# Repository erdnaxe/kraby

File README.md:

# Kraby

Kraby is an hexapod robot.
It is an open source development platform for educational purpose.
It was designed for a Master 1
project at [ENS Paris-Saclay](https://ens-paris-saclay.fr/).

You may read documentation at <https://kraby.readthedocs.io/>

## Build the documentation

Install `mkdocs` then run `mkdocs serve`.

## Install OpenAI environment

```bash
pip install gym_kraby --user
python -m gym_kraby.demo
```

To test servomotors communication with the robot, you may execute `python -m gym_kraby.utils.herkulex_socket`.

## License

This project is under MIT License because we believe in
open development. Please see LICENSE file for more details.

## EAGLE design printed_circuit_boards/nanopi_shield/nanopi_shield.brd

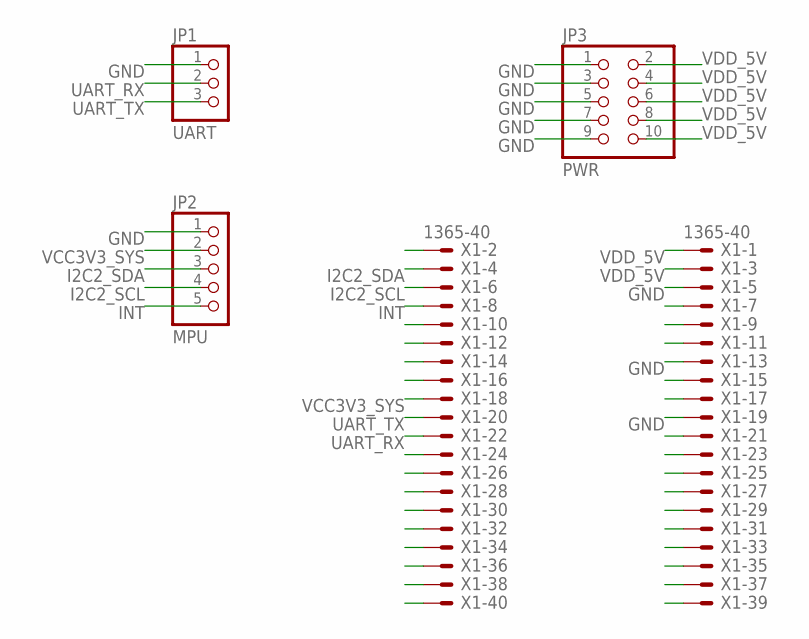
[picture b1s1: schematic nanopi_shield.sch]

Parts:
JP1: UART; 1X03
JP2: MPU; 1X05
JP3: PWR; 2X05
X1: 1365-40

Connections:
GND: JP1.1, JP2.1, JP3.1, JP3.3, JP3.5, JP3.7, JP3.9, X1.5, X1.13, X1.19
I2C2_SCL: JP2.4, X1.6
I2C2_SDA: JP2.3, X1.4
INT: JP2.5, X1.8
UART_RX: JP1.2, X1.22
UART_TX: JP1.3, X1.20
VCC3V3_SYS: JP2.2, X1.18
VDD_5V: JP3.2, JP3.4, JP3.6, JP3.8, JP3.10, X1.1, X1.3

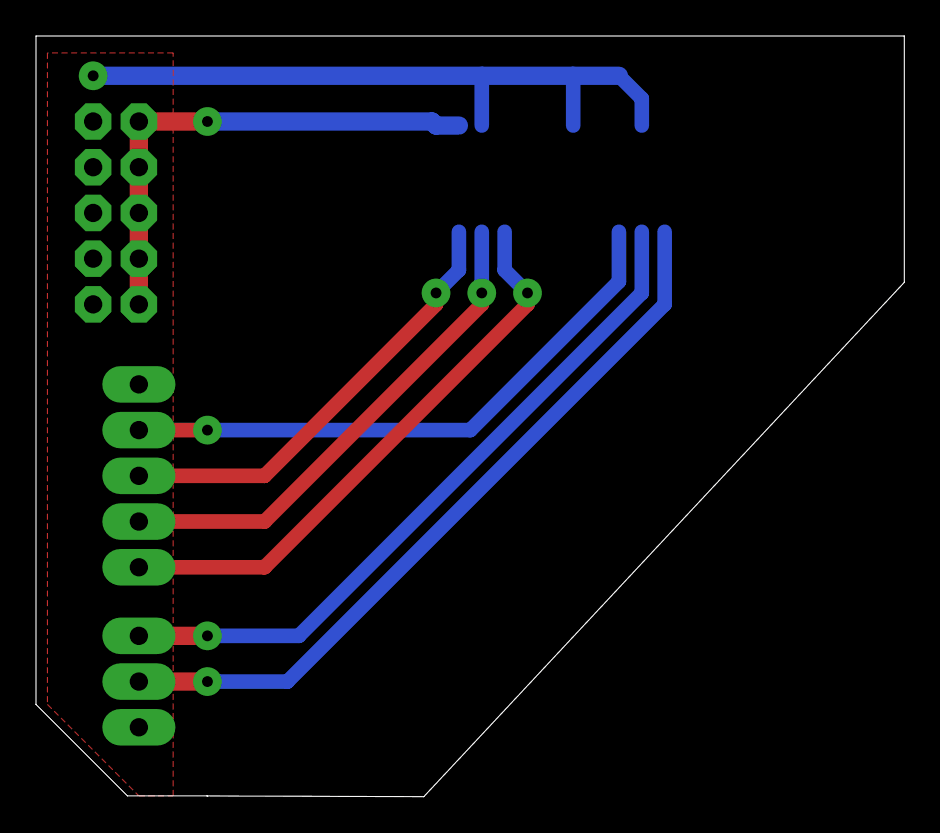
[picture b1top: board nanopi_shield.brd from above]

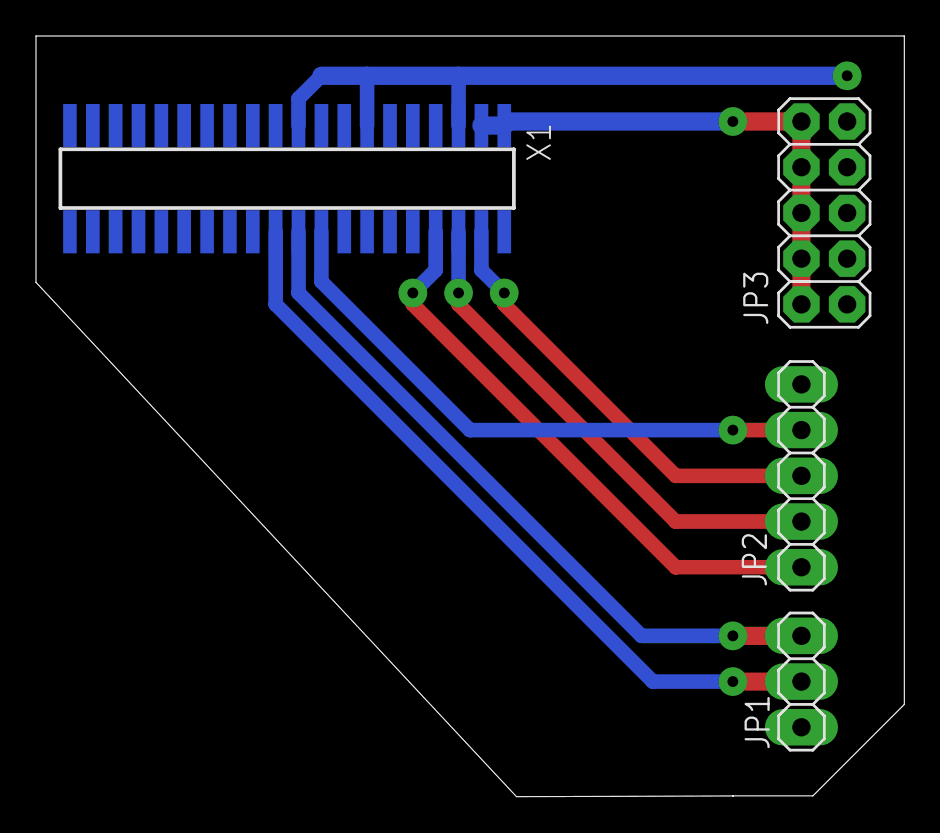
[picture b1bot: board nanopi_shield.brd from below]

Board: 2 copper layers, 48.2 x 42.3 mm, 4 parts (4 on the bottom side), 8 nets.

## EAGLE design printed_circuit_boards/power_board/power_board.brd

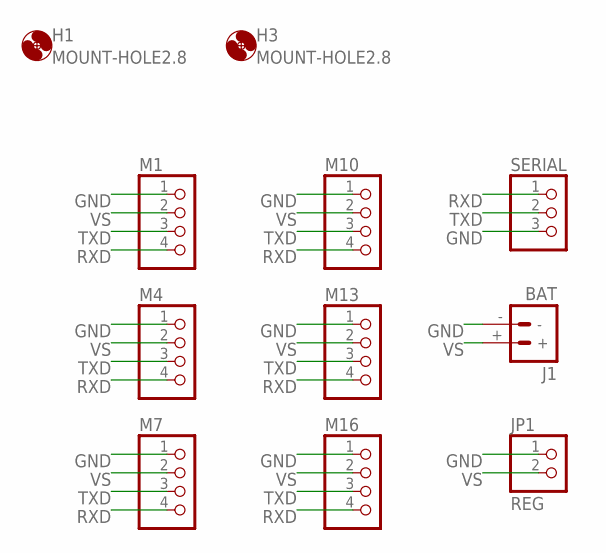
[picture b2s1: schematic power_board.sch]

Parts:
H1, H3: MOUNT-HOLE2.8; 2,8
J1: BAT; DEANS
JP1: REG; 1X02
M1, M4, M7, M10, M13, M16: PINHD-1X4; 1X04
SERIAL: PINHD-1X3; 1X03

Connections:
GND: J1.-, JP1.1, M1.1, M4.1, M7.1, M10.1, M13.1, M16.1, SERIAL.3
RXD: M1.4, M4.4, M7.4, M10.4, M13.4, M16.4, SERIAL.1
TXD: M1.3, M4.3, M7.3, M10.3, M13.3, M16.3, SERIAL.2
VS: J1.+, JP1.2, M1.2, M4.2, M7.2, M10.2, M13.2, M16.2

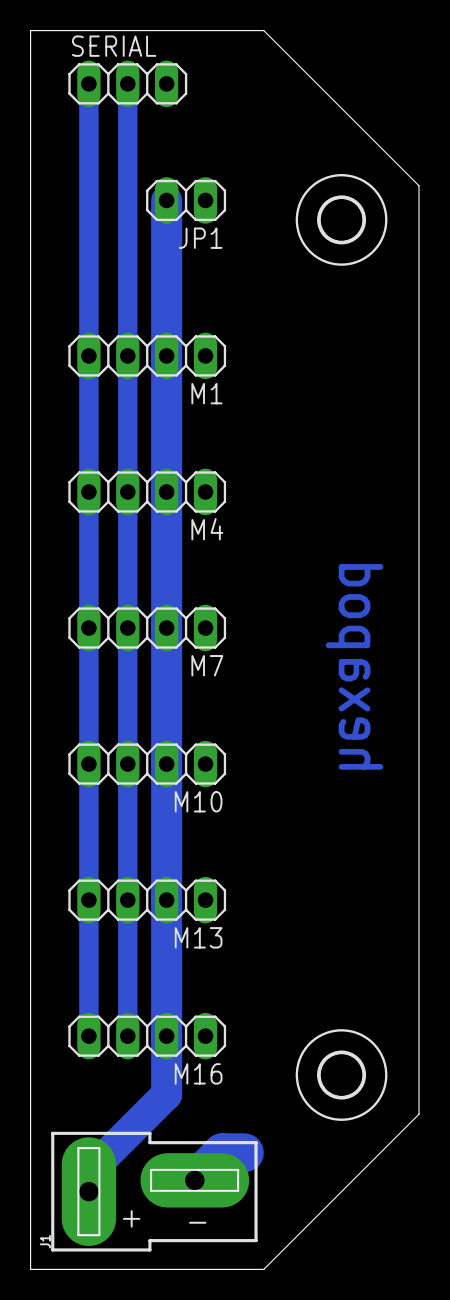
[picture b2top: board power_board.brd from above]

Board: 2 copper layers, 25.3 x 80.8 mm, 11 parts (0 on the bottom side), 4 nets.

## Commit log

2020-02-14 Power board
2020-02-18 Add NanoPi Neo4 shield
2020-02-18 Round corner
2020-02-19 Larger pads
2020-02-19 Add pdf for NanoPi shield
2020-02-19 How to connect
2020-02-20 Larger via
2020-05-18 Easier to solder and fix I2C
2020-05-18 Update power_board eagle version
2020-05-18 Add top and bottom faces render
2020-05-18 Add boards to readme
2020-05-19 MPU9250 interrupt pin
2020-05-19 mkdocs init
2020-05-19 Add 3d parts
2020-05-19 How to patch FriendlyCore
2020-05-19 Format docs/install_nanopi_linux.md
2020-05-19 MPU9250 working
2020-05-19 3d printed parts illustration
2020-05-20 Use non staging MPU9250 driver
2020-05-20 Add iiod instructions
2020-05-22 Use Context for Python iio
2020-05-22 ser2net for motors
2020-05-27 Image in README
2020-06-03 URDF description
2020-06-03 OpenAI Gym environnement
2020-06-03 Implement action_space
2020-06-04 More documentation
2020-06-04 URDF documentation
2020-06-04 URDF: Add core inertia
2020-06-04 GymEnv: Add observation
2020-06-04 Detect fallen robot
2020-06-05 Package OpenAI env
2020-06-08 Include URDF and STL in pip package
2020-06-08 Auto version from git
2020-06-08 Add PyBullet to requirements
2020-06-08 Add contact info in CODE OF CONDUCT
2020-06-08 Travis CI
2020-06-08 Update travis CI configuration
2020-06-08 Remove symlinks and add Pypi description
2020-06-08 Add description to Gym module
2020-06-08 One leg environment
2020-06-08 Keep action and observation in range
2020-06-08 Update one leg env with normalization
2020-06-09 Make OneLeg base static
2020-06-09 Add seed and random initialization
2020-06-09 Clip rather than multiply per 0.99
2020-06-09 Select OneLeg env via command line argument
2020-06-09 Add random mode to demo script
2020-06-09 Fix first servomotor collision
2020-06-09 Implement comsuption reward
2020-06-10 Add Gym environment for reality transfer
2020-06-10 Add OpenAI Gym env documentation
2020-06-10 Reward for one leg
2020-06-10 Add codacy code quality
2020-06-10 Code formatting
2020-06-10 Beautify Markdown
2020-06-10 Fix code block in doc
2020-06-10 Init pyBullet inside environments
2020-06-10 Add max episode step
2020-06-11 Ignore comsuption and do not derivate goal distance
2020-06-11 pytorch-a2c-ppo-acktr-gail training for one leg
2020-06-12 Show goal as crosshair
2020-06-15 Keep the reward positiv
2020-06-15 Add Herkulex helper Python class
2020-06-16 Add Dockerfile for training environment
2020-06-16 Fallback to version 0.0.1 if undefined
2020-06-16 Check env notebook
2020-06-16 OpenAI Spinning Up Dockerfile
2020-06-17 Fix docker spinningup
2020-06-18 Square distance is differentiable
2020-06-18 Inherit RealEnv from BulletEnv
2020-06-18 Docs: split ppo installation from usage
2020-06-18 S_JOG implementation
2020-06-19 Docs: How to launch StableBaselines notebooks
2020-06-19 Notebook for training with StableBaselines
2020-06-19 Render agent notebook
2020-06-19 Working render functions
2020-06-19 Docs: no more patching of pytorch-a2c-ppo-acktr-gail enjoy.py
2020-06-19 Get data from servo in one command
2020-06-19 Docs: More background on servomotors
2020-06-19 Docs: Add link to Herkulex Manual
2020-06-20 Servomotors to 500000bps
2020-06-22 Local motor control test
2020-06-22 Docs: Add diviser for 0.667 Mbps
2020-06-22 More PPO docs
2020-06-22 Docs: fix typo
2020-06-22 Fix #8: loop on recv
2020-06-23 Docs: more about Gym
2020-06-23 Make one leg observations more realistic
2020-06-24 Keep URDF loaded between two episodes
2020-06-24 More optimal way to compute square distance
2020-06-24 Get motorized joints in init
2020-06-25 TimeStep limit using a wrapper
2020-06-25 Reorder bullet init
2020-06-25 set_eeprom for herkulex
2020-06-25 Let's document early training
2020-06-25 Add one leg env screenshot
2020-06-25 Docs: more about observation problem
2020-06-25 Fix typo in index
2020-06-25 Docs: give observation vector
2020-06-26 Add OpenCL support in StableBaselines docker image
2020-06-26 Docs: other PPO implementations
2020-06-26 HexapodEnv: reset position and orientation
2020-06-26 HexapodEnv render target the robot
2020-06-26 RealEnv: Remove servomotors torque
2020-06-29 Fix initial position servomotor bug
2020-06-29 Herkulex velocity control
2020-06-29 Add motor demo video
2020-06-29 Fix #4: hexapod is no longer sliding
2020-06-29 Growing box for one leg objective
2020-06-30 Add OpenGL support in StableBaselines Docker
2020-06-30 Clip velocities
2020-06-30 Test 10 ep in debug gui
2020-06-30 Docs: use note boxes
2020-06-30 Load mkdocs admonition plugin
2020-07-01 Position motor control
2020-07-01 Add an option to reset to neutral position
2020-07-01 Fun script to test motors
2020-07-01 Add doc on socat
2020-07-01 It's faster with UDP
2020-07-01 Send all data
2020-07-02 Fix socat UDP doc and systemd unit
2020-07-02 Better defauts for dance demo
2020-07-02 Update demo video
2020-07-02 Update contact coefficients, see #2
2020-07-02 Render 10 episodes
2020-07-02 Reorder training doc page
2020-07-02 Clean up one leg env
2020-07-03 Reorder one leg training doc
2020-07-03 Notebook to aggregate runs
2020-07-03 Render longer ep
2020-07-03 Clean up training notebook
2020-07-03 Doc: training with random target
2020-07-06 Training without torque in obs
2020-07-06 Add video
2020-07-06 Make sure done is a boolean
2020-07-06 Learning with difference of position to target
2020-07-06 Do not import useless tf modules for reading tensorboards
2020-07-06 Fix typo in doc
2020-07-06 Remove useless files from Docker build context
2020-07-06 Fix permissions for Jupyter Notebooks and lab
2020-07-07 Better hyperparameters and no more fingertip position
2020-07-08 Update real env
2020-07-08 Implement frameskip in envs
2020-07-08 Fix doctring ponctuation (PEP257)
2020-07-09 Use Jupyter lab and add optuna in docker
2020-07-09 Change default env step to 50ms
2020-07-10 New time step
2020-07-14 Add video with 50ms env period
2020-07-14 RealEnv: Wait only if too fast
2020-07-14 RealEnv: Fix sleep
2020-07-14 Update hexapod envs
2020-07-16 Add references page
2020-07-16 More docs
2020-07-17 Docs: more on PPO and better biblio
2020-07-17 Fix JS
2020-07-17 Docs: toc everywhere
2020-07-17 Switch to MIT license
2020-07-17 More references
2020-07-19 Add github action docker
2020-07-21 Monitor and plot results
2020-07-30 Some experiments with one leg
2020-08-11 Add position target in full hexapod env
2020-08-11 Full hexapod training notebook
2020-08-11 Add spinningup notebooks
2020-08-13 Rewrite training one leg doc
2020-08-13 Add other hyperparam
2020-08-14 End of doc one leg
2020-08-14 Update Real world transfer doc
2020-08-24 Add TER doc

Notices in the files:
parts and their libraries:
SparkFun-Connectors: Licensing: Creative Commons ShareAlike 4.0 International - https://creativecommons.org/licenses/by-sa/4.0
